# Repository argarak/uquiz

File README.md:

part of an old project for a CS class i did years ago. archived forever.
i highly recommend not building this. hint: it doesn't work
# uquiz
μquiz - a portable electronic game primarily designed for user-generated multiple-choice quizzes

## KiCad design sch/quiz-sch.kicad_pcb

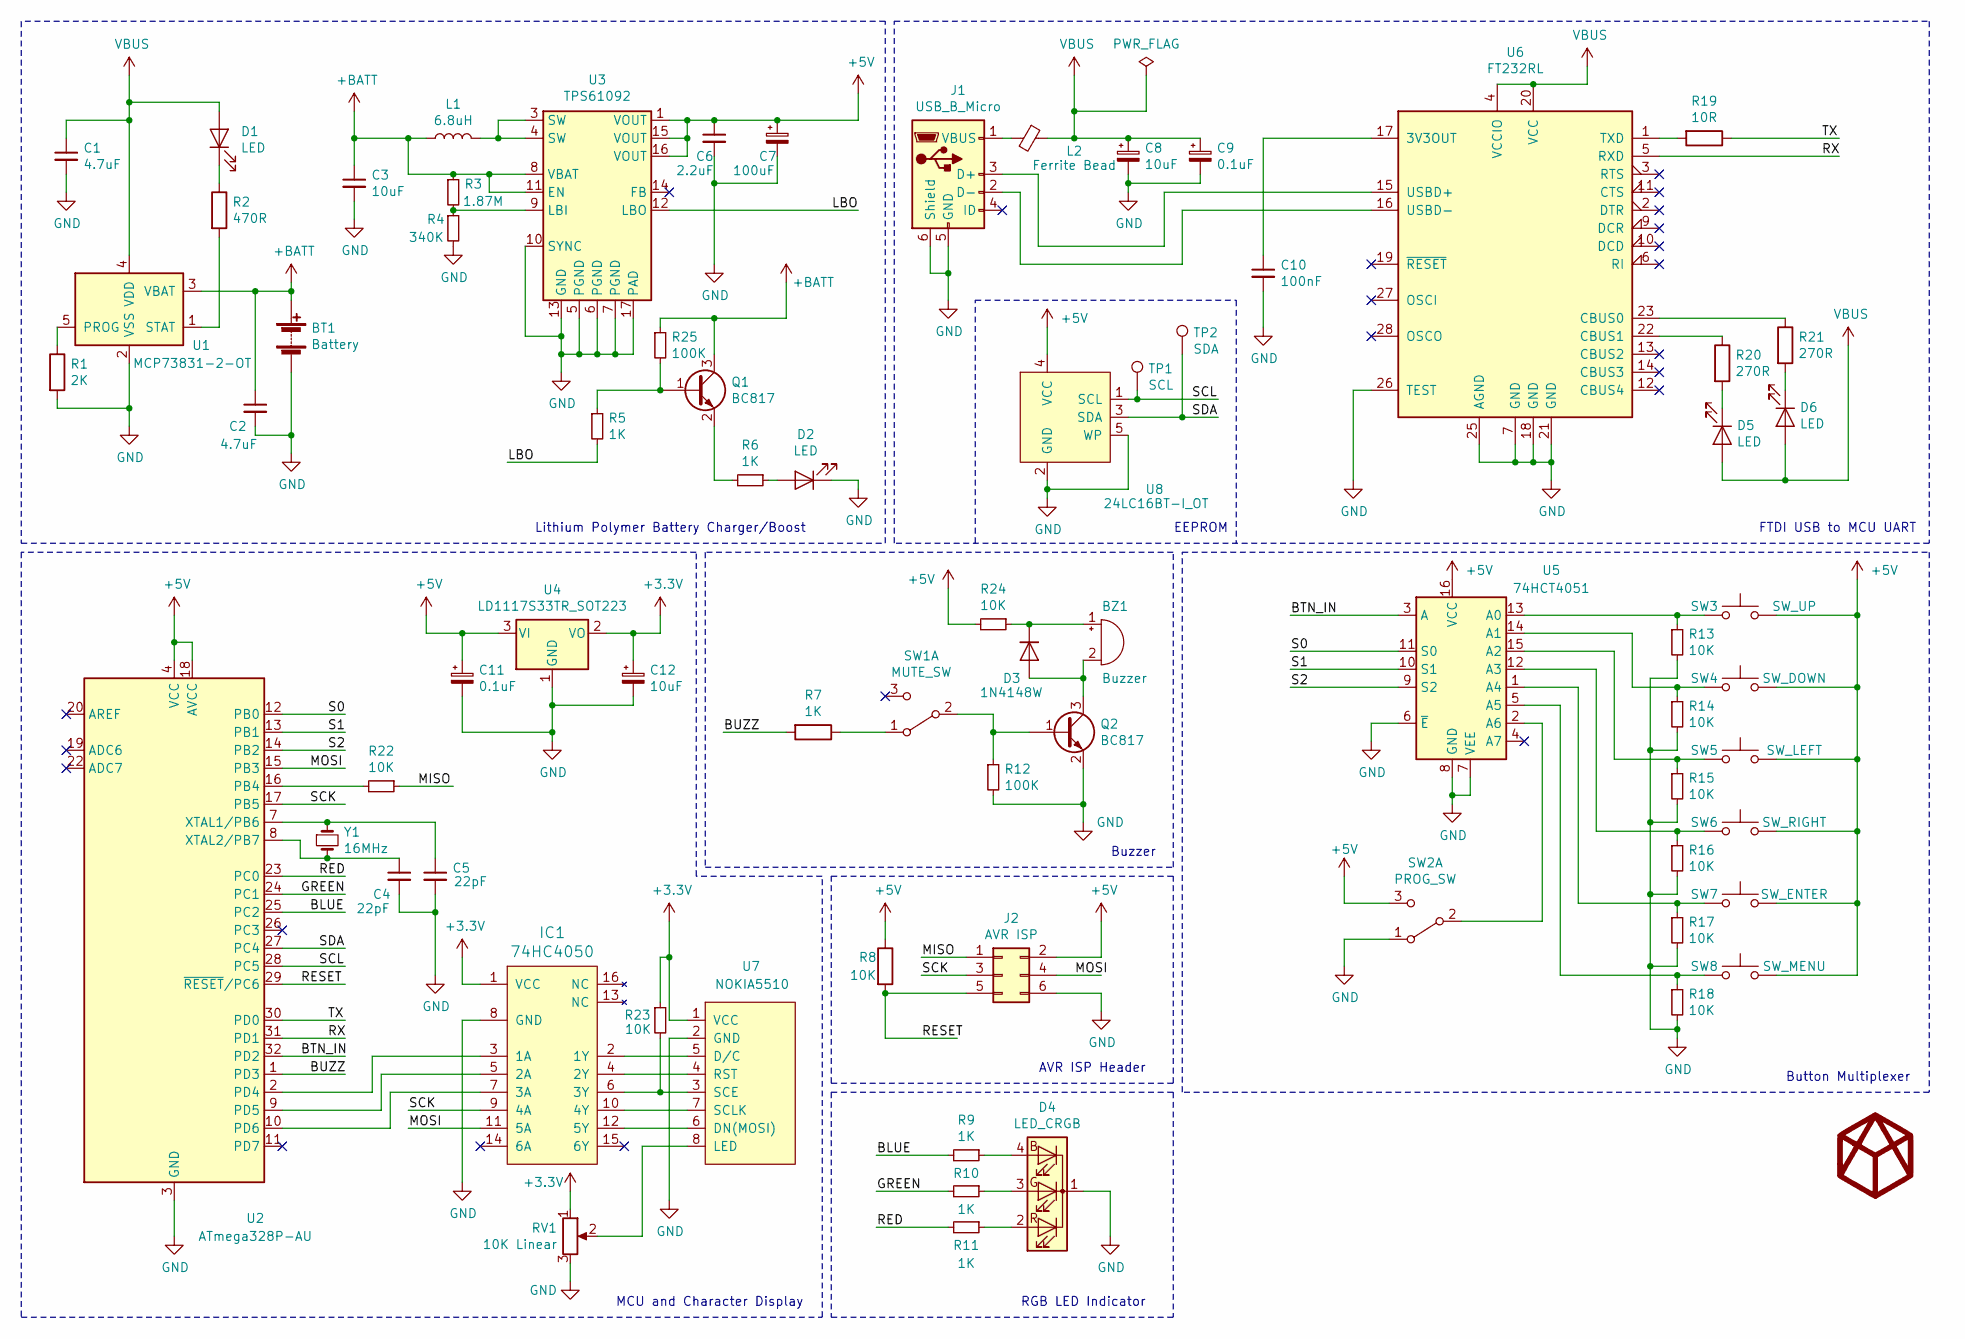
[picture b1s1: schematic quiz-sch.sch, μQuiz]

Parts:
BT1: Battery; JST_PH_S2B-PH-SM4-TB_02x2.00mm_Angled
BZ1: Buzzer; Buzzer_12x9.5RM7.6
C1, C2: 4.7uF; C_1206_HandSoldering
C3: 10uF; C_1206_HandSoldering
C4, C5: 22pF; C_1206_HandSoldering
C6: 2.2uF; C_1206_HandSoldering
C7: 100uF; CP_Elec_6.3x5.3
C8, C12: 10uF; CP_Elec_5x5.3
C9, C11: 0.1uF; CP_Elec_4x5.7
C10: 100nF; C_1206_HandSoldering
D1, D2, D5, D6: LED; LED_0805_HandSoldering
D3: 1N4148W; D_SOD-123
D4: LED_CRGB; LED_RGB_5050-6
IC1: 74HC4050; SOIC-16_3.9x9.9mm_Pitch1.27mm
J1: USB_B_Micro; USB_Micro-B
J2: AVR ISP; Pin_Header_Straight_2x03_Pitch2.54mm
L1: 6.8uH; L_7.3x7.3_H4.5
L2: Ferrite Bead; C_1206_HandSoldering
Q1, Q2: BC817; SOT-23
R1: 2K; R_0805_HandSoldering
R2: 470R; R_0805_HandSoldering
R3: 1.87M; R_0805_HandSoldering
R4: 340K; R_0805_HandSoldering
R5, R6, R7, R9, R10, R11: 1K; R_0805_HandSoldering
R8, R13, R14, R15, R16, R17, R18, R22, R23, R24: 10K; R_0805_HandSoldering
R12, R25: 100K; R_0805_HandSoldering
R19: 10R; R_0805_HandSoldering
R20, R21: 270R; R_0805_HandSoldering
RV1: 10K Linear; Potentiometer_Trimmer-EVM3E
SW1: MUTE_SW; Pin_Header_Straight_1x03_Pitch2.54mm
SW2: PROG_SW; Pin_Header_Straight_1x03_Pitch2.54mm
SW3: SW_UP; SW_PUSH_6mm
SW4: SW_DOWN; SW_PUSH_6mm
SW5: SW_LEFT; SW_PUSH_6mm
SW6: SW_RIGHT; SW_PUSH_6mm
SW7: SW_ENTER; SW_PUSH_6mm
SW8: SW_MENU; SW_PUSH_6mm
TP1: SCL; Pin_Header_Straight_1x01_Pitch2.54mm
TP2: SDA; Pin_Header_Straight_1x01_Pitch2.54mm
U1: MCP73831-2-OT; SOT-23-5_HandSoldering
U2: ATmega328P-AU; TQFP-32_7x7mm_Pitch0.8mm
U3: TPS61092; QFN-16-1EP_4x4mm_Pitch0.65mm
U4: LD1117S33TR_SOT223; SOT-223-3_TabPin2
U5: 74HCT4051; SOIC-16W_7.5x10.3mm_Pitch1.27mm
U6: FT232RL; SSOP-28_5.3x10.2mm_Pitch0.65mm
U7: NOKIA5510; Pin_Header_Straight_1x08_Pitch2.54mm
U8: 24LC16BT-I_OT; SOT-23-5_HandSoldering
Y1: 16MHz; Crystal_SMD_HC49-SD_HandSoldering

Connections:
+3V3: C12.1, IC1.1 (VCC), R23.1, RV1.1, U4.2 (VO), U7.1 (VCC)
+5V: C6.1, C7.1, C11.1, J2.2, R8.1, R24.2, SW2.3 (C), SW3.2, SW4.2, SW5.2, SW6.2, SW7.2, SW8.2, U2.4 (VCC), U2.6 (VCC), U2.18 (AVCC), U3.1 (VOUT), U3.15 (VOUT), U3.16 (VOUT), U4.3 (VI), U5.16 (VCC), U8.4 (VCC)
+BATT: BT1.1 (+), C2.1, C3.1, L1.1, Q1.3 (C), R3.1, R25.1, U1.3 (VBAT), U3.8 (VBAT), U3.11 (EN)
/BLUE: R9.2, U2.25 (PC2)
/BTN_IN: U2.32 (PD2), U5.3 (A)
/BUZZ: R7.2, U2.1 (PD3)
/GREEN: R10.2, U2.24 (PC1)
/LBO: R5.2, U3.12 (LBO)
/MISO: J2.1, R22.1
/MOSI: IC1.11 (5A), J2.4, U2.15 (PB3)
/RED: R11.2, U2.23 (PC0)
/RESET: J2.5, R8.2, U2.29 (~RESET~/PC6)
/RX: U2.31 (PD1), U6.5 (RXD)
/S0: U2.12 (PB0), U5.11 (S0)
/S1: U2.13 (PB1), U5.10 (S1)
/S2: U2.14 (PB2), U5.9 (S2)
/SCK: IC1.9 (4A), J2.3, U2.17 (PB5)
/SCL: TP1.1, U2.28 (PC5), U8.1 (SCL)
/SDA: TP2.1, U2.27 (PC4), U8.3 (SDA)
/TX: R19.1, U2.30 (PD0)
GND: BT1.2 (-), C1.2, C2.2, C3.2, C4.2, C5.2, C6.2, C7.2, C8.2, C9.2, C10.2, C11.2, C12.2, D2.1 (K), D4.1 (K), IC1.8 (GND), J1.5 (GND), J1.6 (Shield), J2.6, Q2.2 (E), R1.2, R4.2, R12.2, R13.2, R14.2, R15.2, R16.2, R17.2, R18.2, RV1.3, SW2.1 (A), U1.2 (VSS), U2.3 (GND), U2.5 (GND), U2.21 (GND), U3.5 (PGND), U3.6 (PGND), U3.7 (PGND), U3.10 (SYNC), U3.13 (GND), U3.17 (PAD), U4.1 (GND), U5.6 (~E), U5.7 (VEE), U5.8 (GND), U6.7 (GND), U6.18 (GND), U6.21 (GND), U6.25 (AGND), U6.26 (TEST), U7.2 (GND), U8.2 (GND), U8.5 (WP)
unnamed: BZ1.1 (-), D3.1 (K), R24.1
unnamed: BZ1.2 (+), D3.2 (A), Q2.3 (C)
unnamed: C4.1, U2.8 (XTAL2/PB7), Y1.2
unnamed: C5.1, U2.7 (XTAL1/PB6), Y1.1
unnamed: C10.1, U6.17 (3V3OUT)
unnamed: D1.1 (K), R2.1
unnamed: D2.2 (A), R6.1
unnamed: D4.2 (RA), R11.1
unnamed: D4.3 (GA), R10.1
unnamed: D4.4 (BA), R9.1
unnamed: D5.1 (K), R20.2
unnamed: D6.1 (K), R21.2
unnamed: IC1.2 (1Y), U7.5 (D/C)
unnamed: IC1.3 (1A), U2.2 (PD4)
unnamed: IC1.4 (2Y), U7.4 (RST)
unnamed: IC1.5 (2A), U2.9 (PD5)
unnamed: IC1.6 (3Y), R23.2, U7.3 (SCE)
unnamed: IC1.7 (3A), U2.10 (PD6)
unnamed: IC1.10 (4Y), U7.7 (SCLK)
unnamed: IC1.12 (5Y), U7.6 (DN(MOSI))
unnamed: J1.1 (VBUS), L2.2
unnamed: J1.2 (D-), U6.16 (USBD-)
unnamed: J1.3 (D+), U6.15 (USBD+)
unnamed: L1.2, U3.3 (SW), U3.4 (SW)
unnamed: Q1.1 (B), R5.1, R25.2
unnamed: Q1.2 (E), R6.2
unnamed: Q2.1 (B), R12.1, SW1.2 (B)
unnamed: R1.1, U1.5 (PROG)
unnamed: R2.2, U1.1 (STAT)
unnamed: R3.2, R4.1, U3.9 (LBI)
unnamed: R7.1, SW1.1 (A)
unnamed: R13.1, SW3.1, U5.13 (A0)
unnamed: R14.1, SW4.1, U5.14 (A1)
unnamed: R15.1, SW5.1, U5.15 (A2)
unnamed: R16.1, SW6.1, U5.12 (A3)
unnamed: R17.1, SW7.1, U5.1 (A4)
unnamed: R18.1, SW8.1, U5.5 (A5)
unnamed: R19.2, U6.1 (TXD)
unnamed: R20.1, U6.22 (CBUS1)
unnamed: R21.1, U6.23 (CBUS0)
unnamed: R22.2, U2.16 (PB4)
unnamed: RV1.2, U7.8 (LED)
unnamed: SW2.2 (B), U5.2 (A6)
VBUS: C1.1, C8.1, C9.1, D1.2 (A), D5.2 (A), D6.2 (A), L2.1, U1.4 (VDD), U6.4 (VCCIO), U6.20 (VCC)

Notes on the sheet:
FTDI USB to MCU UART
Button Multiplexer
AVR ISP Header
RGB LED Indicator
Buzzer
MCU and Character Display
Lithium Polymer Battery Charger/Boost
EEPROM

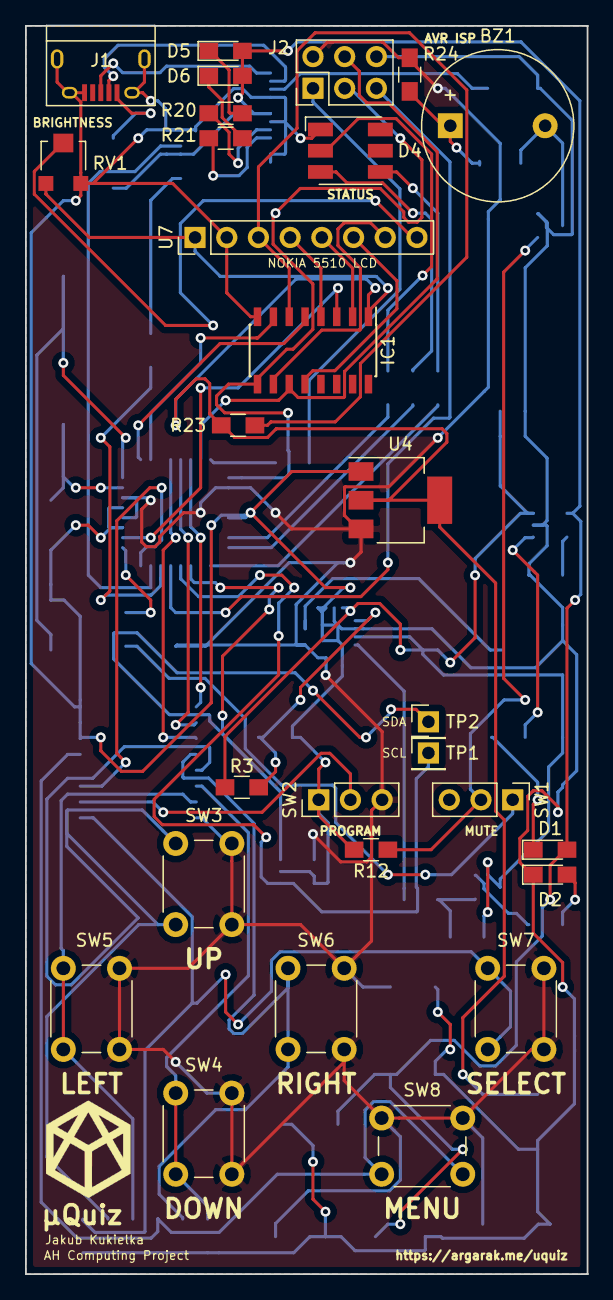
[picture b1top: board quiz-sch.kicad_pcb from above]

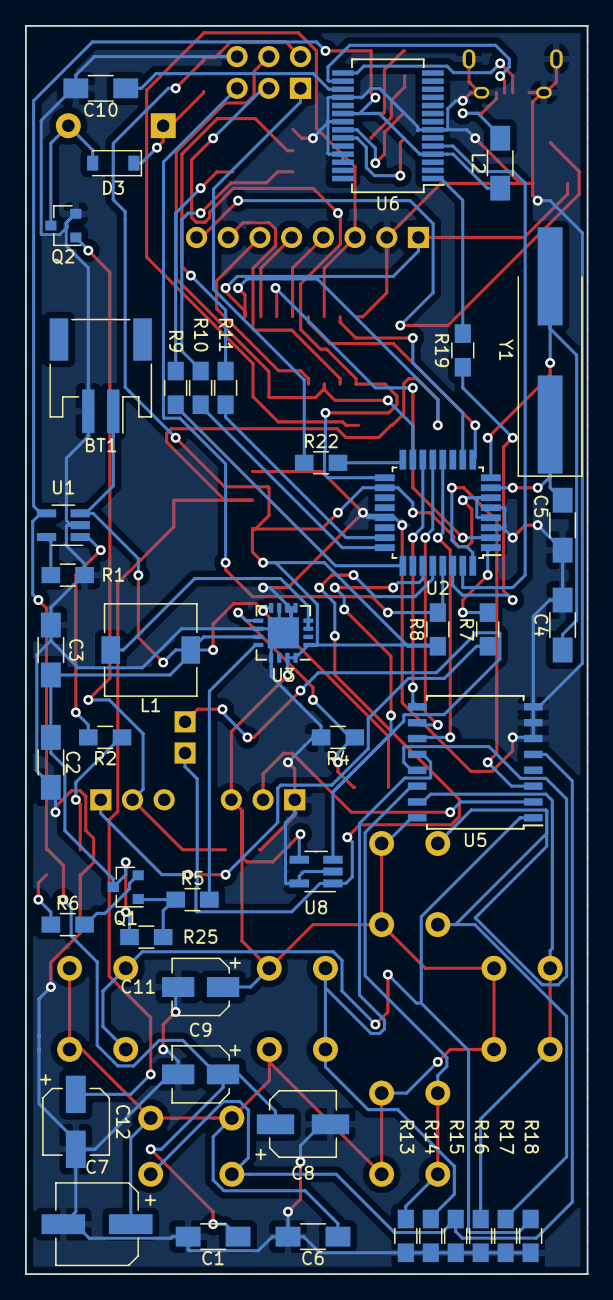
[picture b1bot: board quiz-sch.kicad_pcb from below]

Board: 2 copper layers, 45.0 x 100.0 mm, 72 parts (44 on the bottom side), 65 nets.

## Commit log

2018-10-21 Added schematic
2018-10-21 Removed gitignore as it removed KiCAD libraries
2018-11-13 Added PDF of schematic
2022-11-10 archive notice
